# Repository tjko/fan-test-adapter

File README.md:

# fan-test-adapter
Adapter PCB board for easily testing PC (PWM) fans.

Adapter was created to simplify characterising PC fans. It's mainly meant for PWM fans, but can also be useful for 3-pin PC fans. Adapter also has common JST connectors for common 2-pin fans.
This adapter was used in development and testing of [Fanpico](https://github.com/tjko/fanpico/) (Fanpico is a smart PWM fan controller) to "emulate" motherboard FAN outputs.

Adapter is meant to be used with
* 3 channel programmable power supply (but will work fine with 1 or 2 channel PSUs)
* 2+ channel oscilloscope (or frequency counter)
* 2 channel signal generator

Assembled fan test adapter:

Fan test adapter in use:

## Usage Notes
This is only adapter for easily testing/controlling PWM fans. If used incorrectly it could easily damage your fans, etc...

### Power Connectors
Fan Test Adapter has three DC power jacks. It can be used only with power supplied to "Fan1 Power" jack, but it may be desirable to use all three, depending on how adapter is being used.

#### AUX Power
This is can be used to power the board itself (3.3V power rail, LEDs, etc). This can be useful if doing fan power consumption measurements via measuring supplied power to Fan1/Fan2 connectors.
When using this connector make sure jumper _Aux Power_ is set to _Aux_ position (and _Fan2 Power_ jumper is set to _Fan2_ position).

Recommended supply voltage is 5V (however up to 24V can be used if needed).

#### Fan1 Power
This is used to provide power to Fan1. Additionally _Aux Power_ jumper can be set to _Fan1_ position if _AUX Power_ is not used.

Recommended supply voltage is the nominal voltage of the fan being tested (Voltage should be in range from 5V to 24V max).

#### Fan2 Power
This is used to proive power fo Fan1.  If this connector is used remember to set _Fan2 Power_ jumper to _Fan2_ position.

Recommended supply voltage is the nominal voltage of the fan being tested (Voltage should be in range from 5V to 24V max).

### Jumpers

#### Fan1 Current
Normally closed. Can be used for precise current measurement of Fan1 power consumption, by removing the jumper and connecting current meter in the pins.
#### Fan2 Current
Normally closed. Can be used for precise current measurement of Fan2 power consumption, by removing the jumper and connecting current meter in the pins.
#### Aux Power
Jumper to select whether board itself (3.3V power rail) is powered from _Fan1 Power_ or _Aux Power_ power connector.
#### Fan2 Power
Jumper to select whether Fan2 is powered from _Fan1 Power_ or _Fan2 Power_ power connector.

### BNC Connectors
#### Fan1/Fan2 PWM (Input)
Input for PWM signal to control fan speed. Typically (with PC fans) this is 25kHz PWM signal (0-5V).

#### Fan1/Fan2 Tacho (Output)
Adapter generates 3.3V TTL signal from the open collector tachometer output of the fan. So this is generally safe to be read direcly with a 3.3V (or 5V) MCU.

## Building Notes
* See [PCB](#pcb-kerbers) section for how to get PCB manufactured (currently it is only few dollars pre PCB to have these manufactured).
* List of needed components can be found here: [BOM](fan-test-adapter-bom.csv)
* Some of the components are optional (but can offer some protection) for details see: [Schematic](fan-test-adapter.pdf)

### PCB (Kerbers)
Kerber files ready to be sent to a PCB maker (like JLCPCB, etc):
* [PCB Version 1.2](kerbers/fan-test-adapter-v1.2.zip)

### Where to buy?
Currently this is only a DIY project. However PCBs are occasionally available (in limited quantities) at: [eBay](https://www.ebay.com/usr/oh6lxv)

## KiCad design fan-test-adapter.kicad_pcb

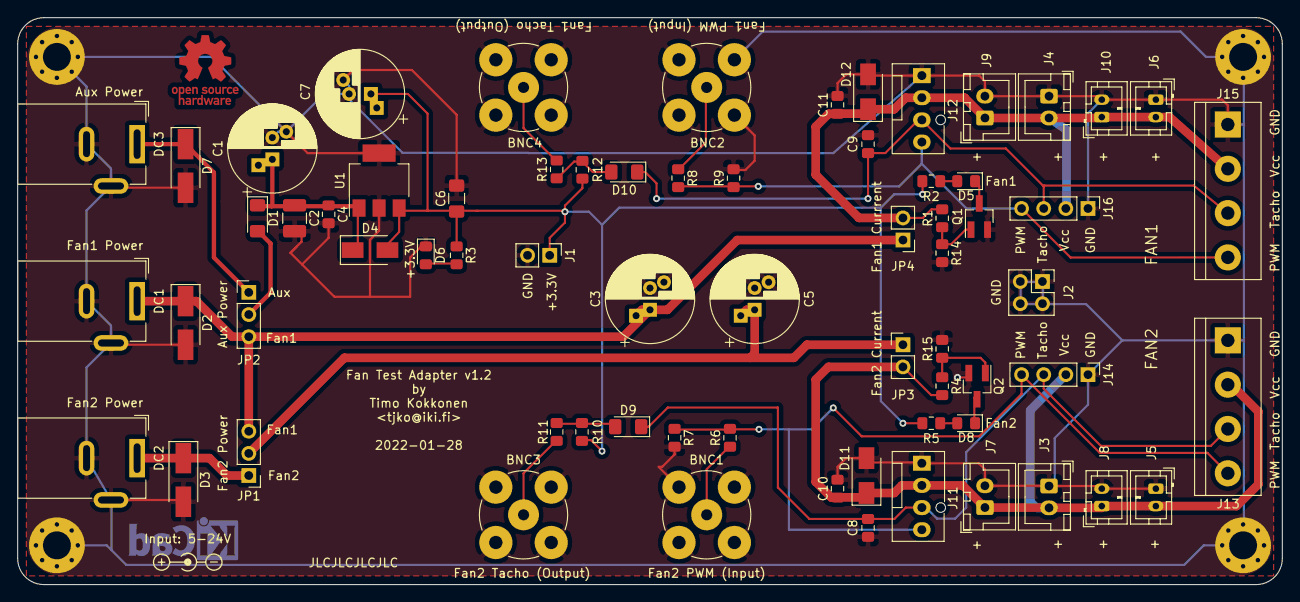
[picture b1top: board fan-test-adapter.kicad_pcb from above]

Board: 2 copper layers, 145.0 x 65.0 mm, 72 parts (0 on the bottom side), 27 nets.

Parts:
BNC1: Fan2 PWM (Input); BNC_TEConnectivity_1478204_Vertical
BNC2: Fan1 PWM (Input); BNC_TEConnectivity_1478204_Vertical
BNC3: Fan2 Tacho (Output); BNC_TEConnectivity_1478204_Vertical
BNC4: Fan1 Tacho (Output); BNC_TEConnectivity_1478204_Vertical
C1: 10uF 35V; CP_Radial_D10.0mm_P2.50mm_P5.00mm
C2: 4.7uF 35V; C_1210_3225Metric_Pad1.42x2.65mm_HandSolder
C3, C5: DNF; CP_Radial_D10.0mm_P2.50mm_P5.00mm
C4: 0.1uF 35V; C_0805_2012Metric_Pad1.15x1.40mm_HandSolder
C6: 10uF; C_1206_3216Metric_Pad1.42x1.75mm_HandSolder
C7: 10uF; CP_Radial_D10.0mm_P2.50mm_P5.00mm
C8, C9: 1nF; C_0805_2012Metric_Pad1.15x1.40mm_HandSolder
C10, C11: 0.1uF; C_0805_2012Metric_Pad1.15x1.40mm_HandSolder
D1, D9, D10: SM5819PL-TP; D_1206_3216Metric_Pad1.42x1.75mm_HandSolder
D2, D3, D7: SBRT5A50SA; D_SMA_Handsoldering
D4, D11, D12: FM4007W; D_SMA
D5, D6, D8: LED; LED_0805_2012Metric_Pad1.15x1.40mm_HandSolder
DC1: Fan1 Power; BarrelJack_Wuerth_6941xx301002
DC2: Fan2 Power; BarrelJack_Wuerth_6941xx301002
DC3: Aux Power; BarrelJack_Wuerth_6941xx301002
H1, H2, H3, H4: MountingHole_Pad; MountingHole_3.2mm_M3_Pad_Via
J1: 3.3V Output; PinHeader_1x02_P2.54mm_Vertical
J2: Extra GND Pins; PinHeader_2x02_P2.54mm_Vertical
J3: Fan2_JST2; JST_XH_B2B-XH-A_1x02_P2.50mm_Vertical
J4: Fan1_JST2; JST_XH_B2B-XH-A_1x02_P2.50mm_Vertical
J5: Fan2_JST4; JST_PH_B2B-PH-K_1x02_P2.00mm_Vertical
J6: Fan1_JST4; JST_PH_B2B-PH-K_1x02_P2.00mm_Vertical
J7: Fan2_JST1; JST_XH_B2B-XH-A_1x02_P2.50mm_Vertical
J8: Fan2_JST3; JST_PH_B2B-PH-K_1x02_P2.00mm_Vertical
J9: Fan1_JST1; JST_XH_B2B-XH-A_1x02_P2.50mm_Vertical
J10: Fan1_JST3; JST_PH_B2B-PH-K_1x02_P2.00mm_Vertical
J11: Fan2; FanPinHeader_1x04_P2.54mm_Vertical
J12: Fan1; FanPinHeader_1x04_P2.54mm_Vertical
J13: Fan2_Terminal; TerminalBlock_bornier-4_P5.08mm
J14: Fan2_Header; PinHeader_1x04_P2.54mm_Vertical
J15: Fan1_Terminal; TerminalBlock_bornier-4_P5.08mm
J16: Fan1_Header; PinHeader_1x04_P2.54mm_Vertical
JP1: Fan2 Power; PinHeader_1x03_P2.54mm_Vertical
JP2: Aux Power; PinHeader_1x03_P2.54mm_Vertical
JP3: Fan2 Current; PinHeader_1x02_P2.54mm_Vertical
JP4: Fan1 Currrent; PinHeader_1x02_P2.54mm_Vertical
Q1, Q2: 2N7002K; SOT-23_Handsoldering
R1, R4, R10, R12: 10k; R_0805_2012Metric_Pad1.15x1.40mm_HandSolder
R2, R3, R5: 5k; R_0805_2012Metric_Pad1.15x1.40mm_HandSolder
R6, R8, R11, R13: 1k; R_0805_2012Metric_Pad1.15x1.40mm_HandSolder
R7, R9: 33k; R_0805_2012Metric_Pad1.15x1.40mm_HandSolder
R14, R15: 1M; R_0805_2012Metric_Pad1.15x1.40mm_HandSolder
U1: SPX2954-3.3; SOT-223-3_TabPin2

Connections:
+3V3: C6.1, C7.1, D4.2, J1.1, R2.1, R3.1, R5.1, R10.1, R12.1, U1.3
Fan1_On: C11.1, D12.1, J4.2, J6.2, J9.1, J10.1, J12.2, J15.2, J16.2, JP4.2, R1.2
Fan2_On: C10.1, D11.1, J3.2, J5.2, J7.1, J8.1, J11.2, J13.2, J14.2, JP3.2, R4.2
GND: BNC1.2, BNC2.2, BNC3.2, BNC4.2, C1.2, C2.2, C3.2, C4.2, C5.2, C6.2, C7.2, C8.2, C9.2, C10.2, C11.2, D2.2, D3.2, D6.1, D7.2, D11.2, D12.2, DC1.2, DC1.3, DC2.2, DC2.3, DC3.2, DC3.3, H1.1, H2.1, H3.1, H4.1, J1.2, J2.1, J2.2, J2.3, J2.4, J3.1, J4.1, J5.1, J6.1, J7.2, J8.2, J9.2, J10.2, J11.1, J12.1, J13.1, J14.1, J15.1, J16.1, Q1.2, Q2.2, R7.2, R9.2, R14.2, R15.2, U1.2
unnamed: BNC1.1, R6.1
unnamed: BNC2.1, R8.1
unnamed: BNC3.1, R11.2
unnamed: BNC4.1, R13.2
unnamed: C1.1, C2.1, C4.1, D1.1, D4.1, U1.1
unnamed: C8.1, D9.1, J11.3, J13.3, J14.3
unnamed: C9.1, D10.1, J12.3, J15.3, J16.3
unnamed: D3.1, DC2.1, JP1.1
unnamed: D5.1, Q1.3
unnamed: D5.2, R2.2
unnamed: D6.2, R3.2
unnamed: D7.1, DC3.1, JP2.1
unnamed: D8.1, Q2.3
unnamed: D8.2, R5.2
unnamed: D9.2, R10.2, R11.1
unnamed: D10.2, R12.2, R13.1
unnamed: J11.4, J13.4, J14.4, R6.2, R7.1
unnamed: J12.4, J15.4, J16.4, R8.2, R9.1
unnamed: Q1.1, R1.1, R14.1
unnamed: Q2.1, R4.1, R15.1
V_aux: D1.2, JP2.2
V_fan1: C3.1, D2.1, DC1.1, JP1.3, JP2.3, JP4.1
V_fan2: C5.1, JP1.2, JP3.1

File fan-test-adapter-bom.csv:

Ref,QTY,Value,Cmp name,Footprint,Description,Vendor,Mouser,LCSC
"BNC1, BNC2, BNC3, BNC4",4,5-1634503-1,Conn_Coaxial,Connector_Coaxial:BNC_TEConnectivity_1478204_Vertical,"coaxial connector (BNC, SMA, SMB, SMC, Cinch/RCA, LEMO, ...)",TE,571-5-1634503-1,
C1,1,4.7uF 35V (DNF),CP,Capacitor_THT:CP_Radial_D10.0mm_P2.50mm_P5.00mm,,,,
"C2,",1,4.7uF 35V,CP,Capacitor_SMD:C_1210_3225Metric_Pad1.42x2.65mm_HandSolder,Tantalum,,581-TAJB475K035R,
"C4, C10, C11,",3,0.1uF 35V,C,Capacitor_SMD:C_0805_2012Metric_Pad1.15x1.40mm_HandSolder,Unpolarized capacitor,,,
"C6,",1,10uF 16V,CP,Capacitor_SMD:C_1206_3216Metric_Pad1.42x1.75mm_HandSolder,Tantalum,,,C880927
"C7,",1,10uF 16V (DNF),CP,Capacitor_THT:CP_Radial_D10.0mm_P2.50mm_P5.00mm,,,,
"C8, C9,",2,1nF,C,Capacitor_SMD:C_0805_2012Metric_Pad1.15x1.40mm_HandSolder,Unpolarized capacitor,,,
"D1, D9, D10,",3,SM5819PL-TP,D,Diode_SMD:D_1206_3216Metric_Pad1.42x1.75mm_HandSolder,Diode,,,C669023
"D2, D3, D7,",3,SBRT5A50SA,D,Diode_SMD:D_SMA_Handsoldering,Diode,,,C264107
"D4, D11, D12,",3,FM4007W,D,Diode_SMD:D_SMA,Diode,,,C402244
"D5, D6, D8,",3,LED,LED,LED_SMD:LED_0805_2012Metric_Pad1.15x1.40mm_HandSolder,Light emitting diode,,,C434432
"DC1, DC2, DC3",3,DC Jack,Barrel_Jack_Switch,Connector_BarrelJack:BarrelJack_Wuerth_6941xx301002,DC Barrel Jack with an internal switch,,,
"J3, J4, J7, J9",4,JST XH,Conn_01x02_Male,Connector_JST:JST_XH_B2B-XH-A_1x02_P2.50mm_Vertical,,,,C158012
"J5, J6, J8, J10",4,JST PH,Conn_01x02_Male,Connector_JST:JST_PH_B2B-PH-K_1x02_P2.00mm_Vertical,,,,C131337
"J11, J12",2,47053-1000,Fan_CPU_4pin,Connector:FanPinHeader_1x04_P2.54mm_Vertical,"CPU Fan, tacho output, PWM input, 4-pin connector",Molex,538-47053-1000,
"J13, J15",2,Terminal Block,Conn_01x04_Male,TerminalBlock:TerminalBlock_bornier-4_P5.08mm,,,,C1509679
"Q1, Q2,",2,2N7002K,2N7002K,Package_TO_SOT_SMD:SOT-23_Handsoldering,"0.38A Id, 60V Vds, N-Channel MOSFET, SOT-23",,,C85047
"R1, R4,",2,100k,R,Resistor_SMD:R_0805_2012Metric_Pad1.15x1.40mm_HandSolder,Resistor,,,
"R2, R3, R5,",3,5k,R,Resistor_SMD:R_0805_2012Metric_Pad1.15x1.40mm_HandSolder,Resistor,,,
"R6, R8, R11, R13,",4,1k,R,Resistor_SMD:R_0805_2012Metric_Pad1.15x1.40mm_HandSolder,Resistor,,,
"R7, R9,",2,33k,R,Resistor_SMD:R_0805_2012Metric_Pad1.15x1.40mm_HandSolder,Resistor,,,
"R10, R12,",2,10k,R,Resistor_SMD:R_0805_2012Metric_Pad1.15x1.40mm_HandSolder,Resistor,,,
"R14, R15,",2,1M,R,Resistor_SMD:R_0805_2012Metric_Pad1.15x1.40mm_HandSolder,Resistor,,,
"U1,",1,SPX2954-3.3,SPX2954-3.3,Package_TO_SOT_SMD:SOT-223-3_TabPin2,"400mA Low drop-out regulator, Fixed Output 3.3V, SOT-223",,,C32770
Jumpers,4,2.54mm jumper,,,,,,C5305

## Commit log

2022-02-08 Add KiCad project files.
2022-02-08 Add kerbers for v1.2 PCB.
2022-02-08 Add some photos.
2022-02-08 Add PDF of the schematic.
2022-02-08 Correct component values.
2022-02-12 Add bill of materials (BOM).
2022-02-12 Add part number for DC jack.
